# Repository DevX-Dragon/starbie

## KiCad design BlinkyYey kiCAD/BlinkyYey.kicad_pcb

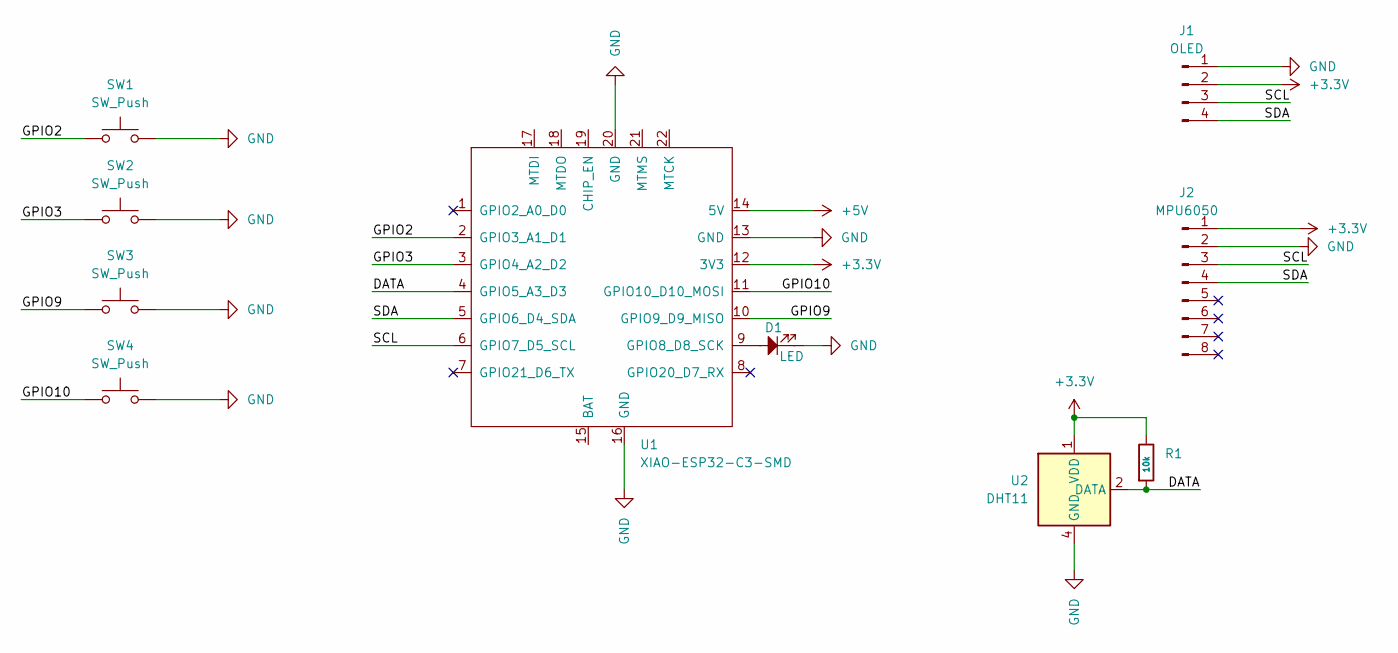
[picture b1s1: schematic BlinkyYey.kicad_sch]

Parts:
D1: LED; LED_D5.0mm
J1: OLED; 128x64OLED
J2: MPU6050; PinHeader_1x08_P2.54mm_Vertical
R1: 10k; R_Axial_DIN0204_L3.6mm_D1.6mm_P7.62mm_Horizontal
SW1, SW2, SW3, SW4: SW_Push; SW_Cherry_MX_1.00u_PCB
U1: XIAO-ESP32-C3-SMD; XIAO-ESP32C3-SMD
U2: DHT11; Aosong_DHT11_5.5x12.0_P2.54mm

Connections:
+3.3V: J1.2, J2.1, R1.1, U1.12 (3V3), U2.1 (VDD)
+5V: U1.14 (5V)
/DATA: R1.2, U1.4 (GPIO5_A3_D3), U2.2 (DATA)
/GPIO2: SW1.1, U1.2 (GPIO3_A1_D1)
/GPIO3: SW2.1, U1.3 (GPIO4_A2_D2)
/GPIO9: SW3.1, U1.10 (GPIO9_D9_MISO)
/GPIO10: SW4.1, U1.11 (GPIO10_D10_MOSI)
/SCL: J1.3, J2.3, U1.6 (GPIO7_D5_SCL)
/SDA: J1.4, J2.4, U1.5 (GPIO6_D4_SDA)
GND: D1.1, J1.1, J2.2, SW1.2, SW2.2, SW3.2, SW4.2, U1.13 (GND), U1.16 (GND), U1.20 (GND), U2.4 (GND)
unnamed: D1.2, U1.9 (GPIO8_D8_SCK)

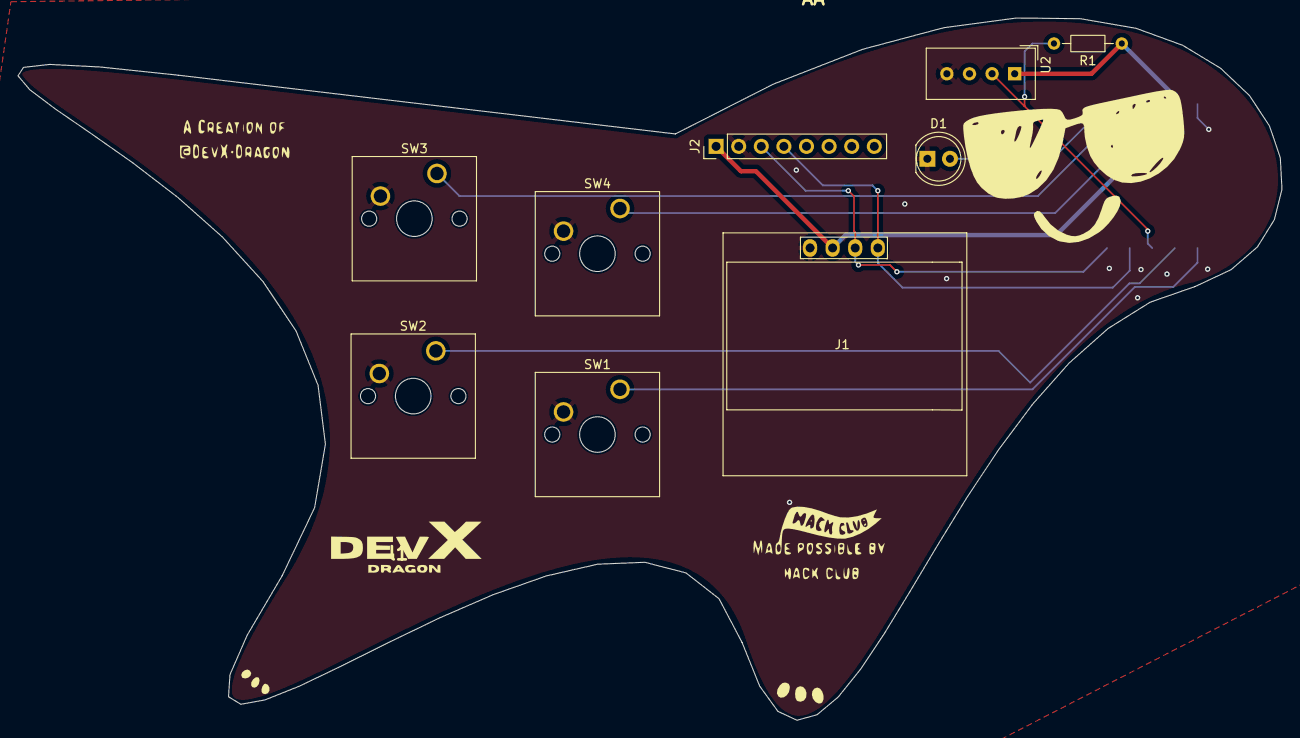
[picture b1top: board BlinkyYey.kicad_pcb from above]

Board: 2 copper layers, 142.0 x 78.9 mm, 12 parts (1 on the bottom side), 10 nets.

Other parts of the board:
AA: LOGO
l1: LOGO; White DevX Official Logo

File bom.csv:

Item Name, Price ,Use,Supplier
PCB Board, $10.00 ,Circuit,JLC PCB
OLED (0.91), $-   ,Display ,(Available in Hand)
MPU6050, $2.00 ,Accelerometer,duino.lk
DHT11, $1.00 ,Temp / Humidity Sensor,duino.lk
Keyswitches and KeyCaps, $-   ,Buttons,available
esp32 c3, $-   ,MCU,available
Shipping + TAX, $20.00 ,,
TOTAL, $33.00 ,,
